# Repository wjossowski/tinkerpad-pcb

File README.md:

# tinkerpad

Programmable 4x4 Macropad with KMK

### Libraries:

- [GitHub - ebastler/marbastlib: A library collecting MX and Choc style footprints, as well as various other parts used to design custom keyboards](https://github.com/ebastler/marbastlib)

- [GitHub - foostan/kbd: for building keyboard libraries](https://github.com/foostan/kbd)

- [GitHub - ncarandini/KiCad-RP-Pico: A simple repository of files needed to add a 3D footprint of the Raspberry Pi Pico board to KiCad.](https://github.com/ncarandini/KiCad-RP-Pico)

### Todo (V3):

- [ ] RGB diode per key
- [ ] Serial interface plugins (UART, SPI)

### V2:

- [x] Chiral (flippable) board
- [x] Columnar stagger

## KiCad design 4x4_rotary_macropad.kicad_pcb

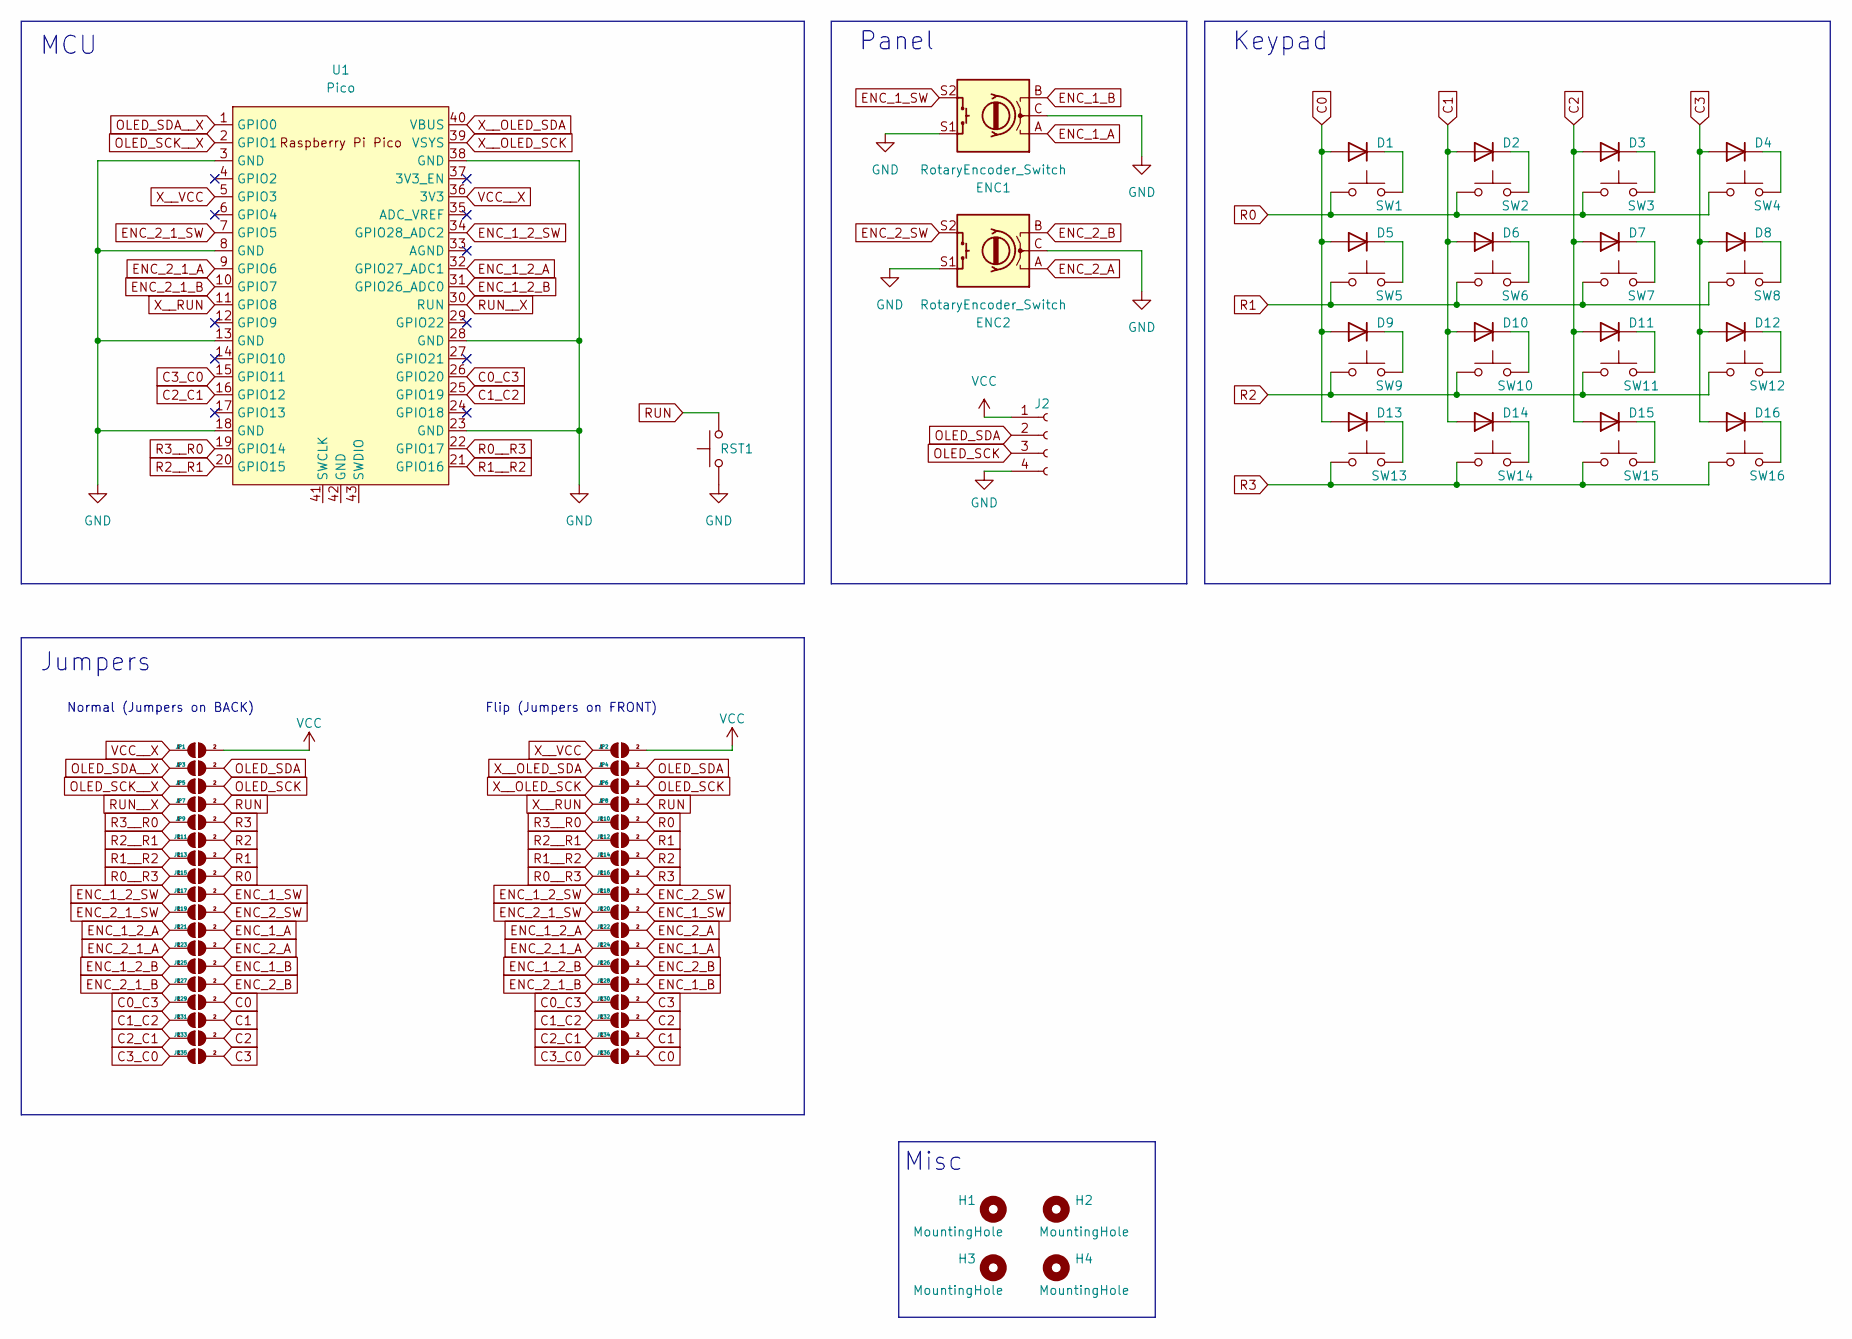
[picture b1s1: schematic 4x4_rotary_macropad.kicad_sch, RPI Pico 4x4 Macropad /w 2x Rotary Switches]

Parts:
D1, D2, D3, D4, D5, D6, D7, D8, D9, D10, D11, D12, D13, D14, D15, D16: e; D3_TH_SMD_v2
ENC1, ENC2: RotaryEncoder_Switch; RotaryEncoder_Alps_EC12E-Switch_Vertical_H20mm
H1, H2, H3, H4: MountingHole; MountingHole_2.2mm_M2
J2: Conn_01x04_Socket; Hirose_DF13-04P-1.25DSA_1x04_P1.25mm_Vertical
JP1, JP2, JP3, JP4, JP5, JP6, JP7, JP8, JP9, JP10, JP11, JP12, JP13, JP14, JP15, JP16, JP17, JP18, JP19, JP20, JP21, JP22, JP23, JP24, JP25, JP26, JP27, JP28, JP29, JP30, JP31, JP32, JP33, JP34, JP35, JP36: SolderJumper_2_Open; jumper
RST1: SW_Push; SW_SKHLLCA010
SW1, SW2, SW3, SW4, SW5, SW6, SW7, SW8, SW9, SW10, SW11, SW12, SW13, SW14, SW15, SW16: SW_Push; SW_Cherry_MX_PCB_1.00u
U1: Pico; RPi_Pico_SMD_TH

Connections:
C0: D1.2 (A), D5.2 (A), D9.2 (A), D13.2 (A), JP29.2 (B), JP36.2 (B)
C0_C3: JP29.1 (A), JP30.1 (A), U1.26 (GPIO20)
C1: D2.2 (A), D6.2 (A), D10.2 (A), D14.2 (A), JP31.2 (B), JP34.2 (B)
C1_C2: JP31.1 (A), JP32.1 (A), U1.25 (GPIO19)
C2: D3.2 (A), D7.2 (A), D11.2 (A), D15.2 (A), JP32.2 (B), JP33.2 (B)
C2_C1: JP33.1 (A), JP34.1 (A), U1.16 (GPIO12)
C3: D4.2 (A), D8.2 (A), D12.2 (A), D16.2 (A), JP30.2 (B), JP35.2 (B)
C3_C0: JP35.1 (A), JP36.1 (A), U1.15 (GPIO11)
ENC_1_2_A: JP21.1 (A), JP22.1 (A), U1.32 (GPIO27_ADC1)
ENC_1_2_B: JP25.1 (A), JP26.1 (A), U1.31 (GPIO26_ADC0)
ENC_1_2_SW: JP17.1 (A), JP18.1 (A), U1.34 (GPIO28_ADC2)
ENC_1_A: ENC1.A, JP21.2 (B), JP24.2 (B)
ENC_1_B: ENC1.B, JP25.2 (B), JP28.2 (B)
ENC_1_SW: ENC1.S2, JP17.2 (B), JP20.2 (B)
ENC_2_1_A: JP23.1 (A), JP24.1 (A), U1.9 (GPIO6)
ENC_2_1_B: JP27.1 (A), JP28.1 (A), U1.10 (GPIO7)
ENC_2_1_SW: JP19.1 (A), JP20.1 (A), U1.7 (GPIO5)
ENC_2_A: ENC2.A, JP22.2 (B), JP23.2 (B)
ENC_2_B: ENC2.B, JP26.2 (B), JP27.2 (B)
ENC_2_SW: ENC2.S2, JP18.2 (B), JP19.2 (B)
GND: ENC1.C, ENC1.S1, ENC2.C, ENC2.S1, J2.4, RST1.1, U1.3 (GND), U1.8 (GND), U1.13 (GND), U1.18 (GND), U1.23 (GND), U1.28 (GND), U1.38 (GND)
unnamed: D1.1 (K), SW1.2
unnamed: D2.1 (K), SW2.2
unnamed: D3.1 (K), SW3.2
unnamed: D4.1 (K), SW4.2
unnamed: D5.1 (K), SW5.2
unnamed: D6.1 (K), SW6.2
unnamed: D7.1 (K), SW7.2
unnamed: D8.1 (K), SW8.2
unnamed: D9.1 (K), SW9.2
unnamed: D10.1 (K), SW10.2
unnamed: D11.1 (K), SW11.2
unnamed: D12.1 (K), SW12.2
unnamed: D13.1 (K), SW13.2
unnamed: D14.1 (K), SW14.2
unnamed: D15.1 (K), SW15.2
unnamed: D16.1 (K), SW16.2
OLED_SCK: J2.3, JP5.2 (B), JP6.2 (B)
OLED_SCK__X: JP5.1 (A), U1.2 (GPIO1)
OLED_SDA: J2.2, JP3.2 (B), JP4.2 (B)
OLED_SDA__X: JP3.1 (A), U1.1 (GPIO0)
R0: JP10.2 (B), JP15.2 (B), SW1.1, SW2.1, SW3.1, SW4.1
R0__R3: JP15.1 (A), JP16.1 (A), U1.22 (GPIO17)
R1: JP12.2 (B), JP13.2 (B), SW5.1, SW6.1, SW7.1, SW8.1
R1__R2: JP13.1 (A), JP14.1 (A), U1.21 (GPIO16)
R2: JP11.2 (B), JP14.2 (B), SW9.1, SW10.1, SW11.1, SW12.1
R2__R1: JP11.1 (A), JP12.1 (A), U1.20 (GPIO15)
R3: JP9.2 (B), JP16.2 (B), SW13.1, SW14.1, SW15.1, SW16.1
R3__R0: JP9.1 (A), JP10.1 (A), U1.19 (GPIO14)
RUN: JP7.2 (B), JP8.2 (B), RST1.2
RUN__X: JP7.1 (A), U1.30 (RUN)
VCC: J2.1, JP1.2 (B), JP2.2 (B)
VCC__X: JP1.1 (A), U1.36 (3V3)
X__OLED_SCK: JP6.1 (A), U1.39 (VSYS)
X__OLED_SDA: JP4.1 (A), U1.40 (VBUS)
X__RUN: JP8.1 (A), U1.11 (GPIO8)
X__VCC: JP2.1 (A), U1.5 (GPIO3)

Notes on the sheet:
Keypad
Misc
Jumpers
Flip (Jumpers on FRONT)
Normal (Jumpers on BACK)
MCU
Panel

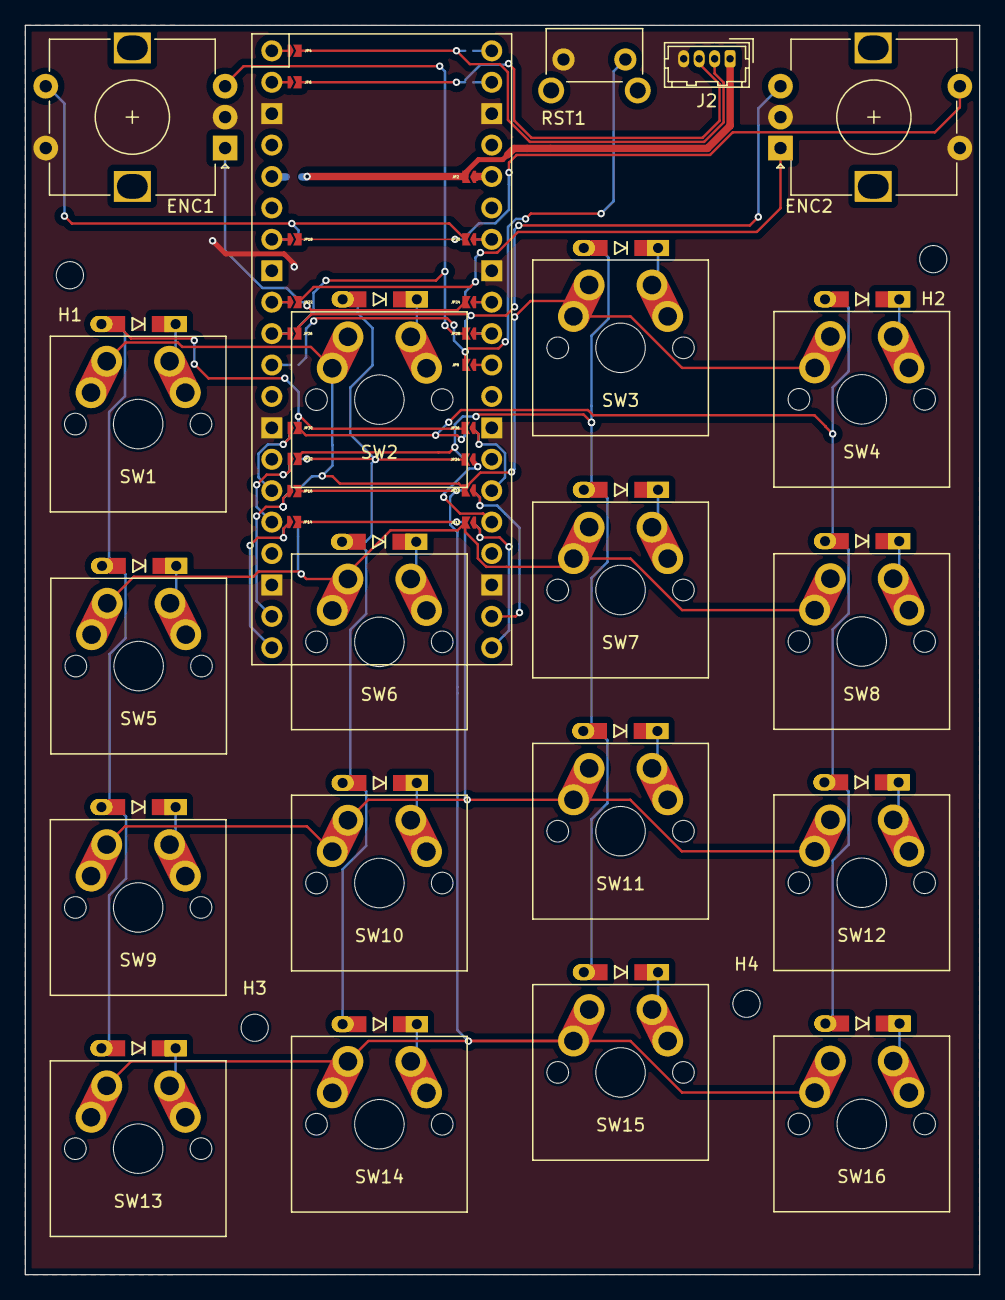
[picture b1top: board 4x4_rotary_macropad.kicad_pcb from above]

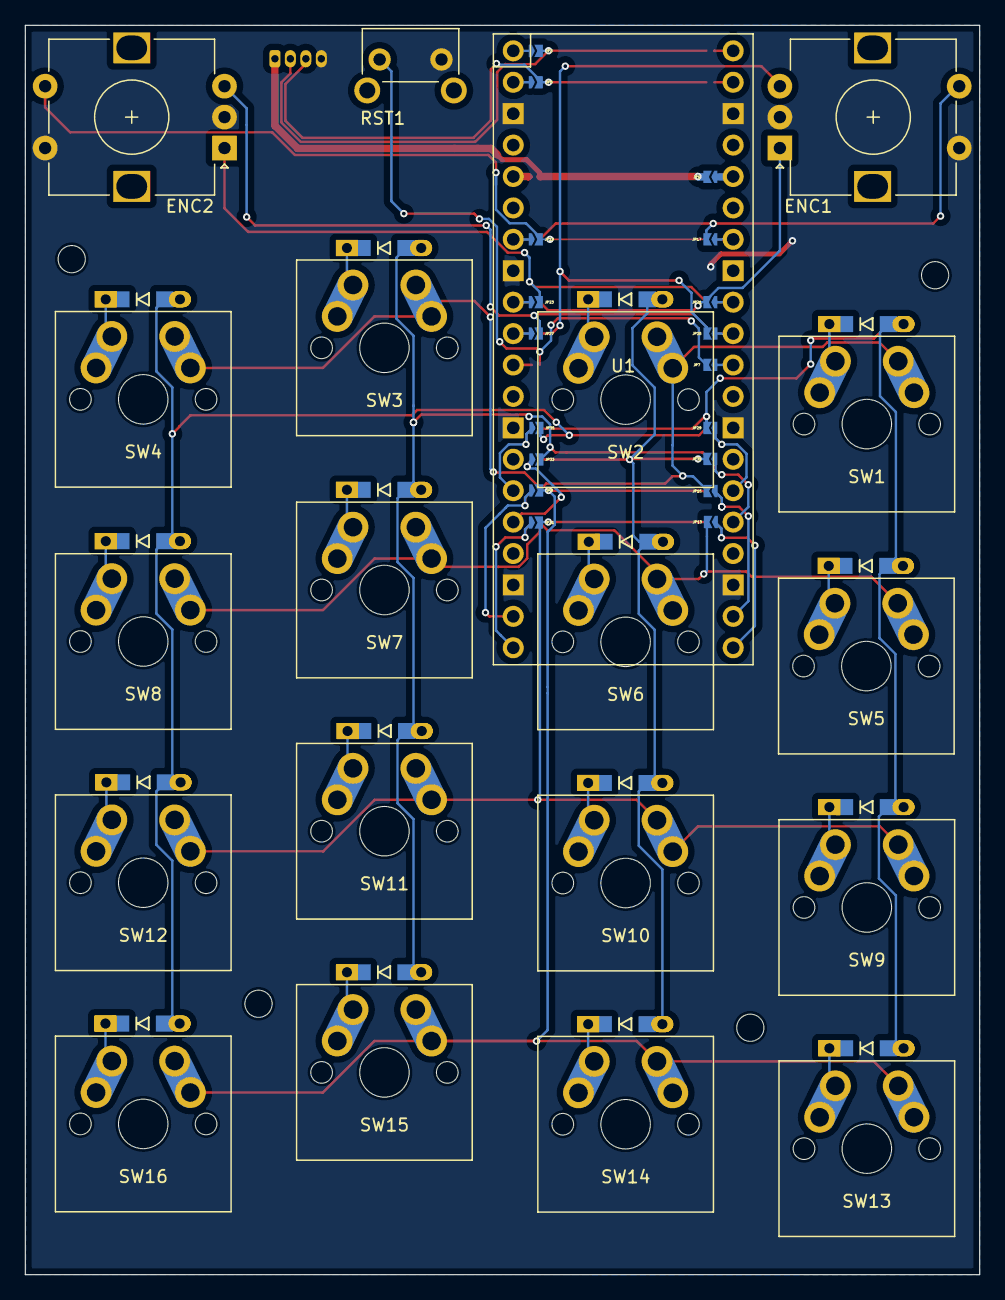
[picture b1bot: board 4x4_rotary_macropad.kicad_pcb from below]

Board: 2 copper layers, 77.1 x 101.0 mm, 77 parts (37 on the bottom side), 57 nets.

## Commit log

2023-05-01 Added KiCad .gitignore rules
2023-05-01 Added PCB Rev 0.2
2023-05-01 Fixed JLCPCB constraints errors
2023-05-01 Added missing libraries
2023-05-02 Updated PCB properties
